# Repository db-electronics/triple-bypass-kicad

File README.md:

# Triple Bypass Version 2
This is a redesign of the fantastic 3bp from dbElectronics.  The goal of this project was to take the initial design and accommodate all models on one pcb without the need to swap parts. It was a team effort between myself, Retrorgb, and Jose Cruz who did the majorty of the testing. Ace, FirebrandX and Mobiusstriptech all were part of the group that helped with the redesign and added various ideas and suggestions that lead to the final product.  The audio adjustment work was done with the help of the mdFourier tool by Artemio Urbina found here - 
https://github.com/ArtemioUrbina/MDFourier.  Artemio and Bfbii stayed up many late nights and helped me run mdFourier to get the levels to match as close as we could to a model 1 va3 genesis.

# Installation Instructions

Currently I suggest using the Audio installation instructions from the mega amp 2.0
http://www.sega-16.com/forum/showthread.php?31989-Take-your-Genesis-audio-to-the-next-level-The-Mega-Amp-2-0-is-here!

For rgb bypass instructions, please see https://www.retrorgb.com/genesistriplebypass.html for now. I will continue working on getting more up-to-date instructions.

# Confirmed Working
The current version of this is working with no issues and has been tested and measured with mdFourier. There are still some systems where the pull down jumpers have not been confirmed.  If you notice any issues, please let me know.
# Design Files
I designed this using the online software tool Easyeda. While I have made the file open for people to edit, I have not yet been able to allow for the files to be truly open source.  This is a work in progress and if I have to remake everything from scratch in Kicad. The files here will always be the most up to date versions. 
# Change Log 17/03/2020
I have added a kicad file to the folder.  it looks ok but I still see some issues with ground layers.  I am new to kicad but this pretty damn close.  As it stands, I still recommend using the current gerber files to send to a pcd fab.  The design files are good to go if you want to to change or modify the design.  
# Change Log 06/03/2020
- Changed the jumper settings on the silk screen to match new info from Jose Cruz that the model 2 va4 has all of the 75 ohm pulldowns on the Genesis. Nothing needs to be changed on the previous versions.  Just take note when installing in a model 2 va4.
# Change Log from V1
 - Added jumpers so that all pulldowns could be enabled or disabled without switching parts.
 - Added AC coupling capacitors on the input of the ths7374 to accommodate for systems that we have not measured or installed in yet.
 - Changed the op amp to a soic8 footprint to accommodate a larger variety of possible op amps.
 - Changed the op amp to a tl972 low noise op amp.
 - Lowered the overall volume and increased resistance to try and alleviate some of the clipping in the louder games.
 - Changed the resistor values and numbering to try and fit on the smaller board.
 - Changed audio and video capacitors to tantalum to accommodate for a bottom mount. 
 - Adjusted and tested installation in a model 1 Genesis. 
 - Increased the audio output capacitors to 47uf.
 - Shrunk the overall size and move the din to the middle of the board to try to avoid the power jacks on a bottom install. 
 - Changed the Low pass filter to a solder jumper that will enable when it is jumped.

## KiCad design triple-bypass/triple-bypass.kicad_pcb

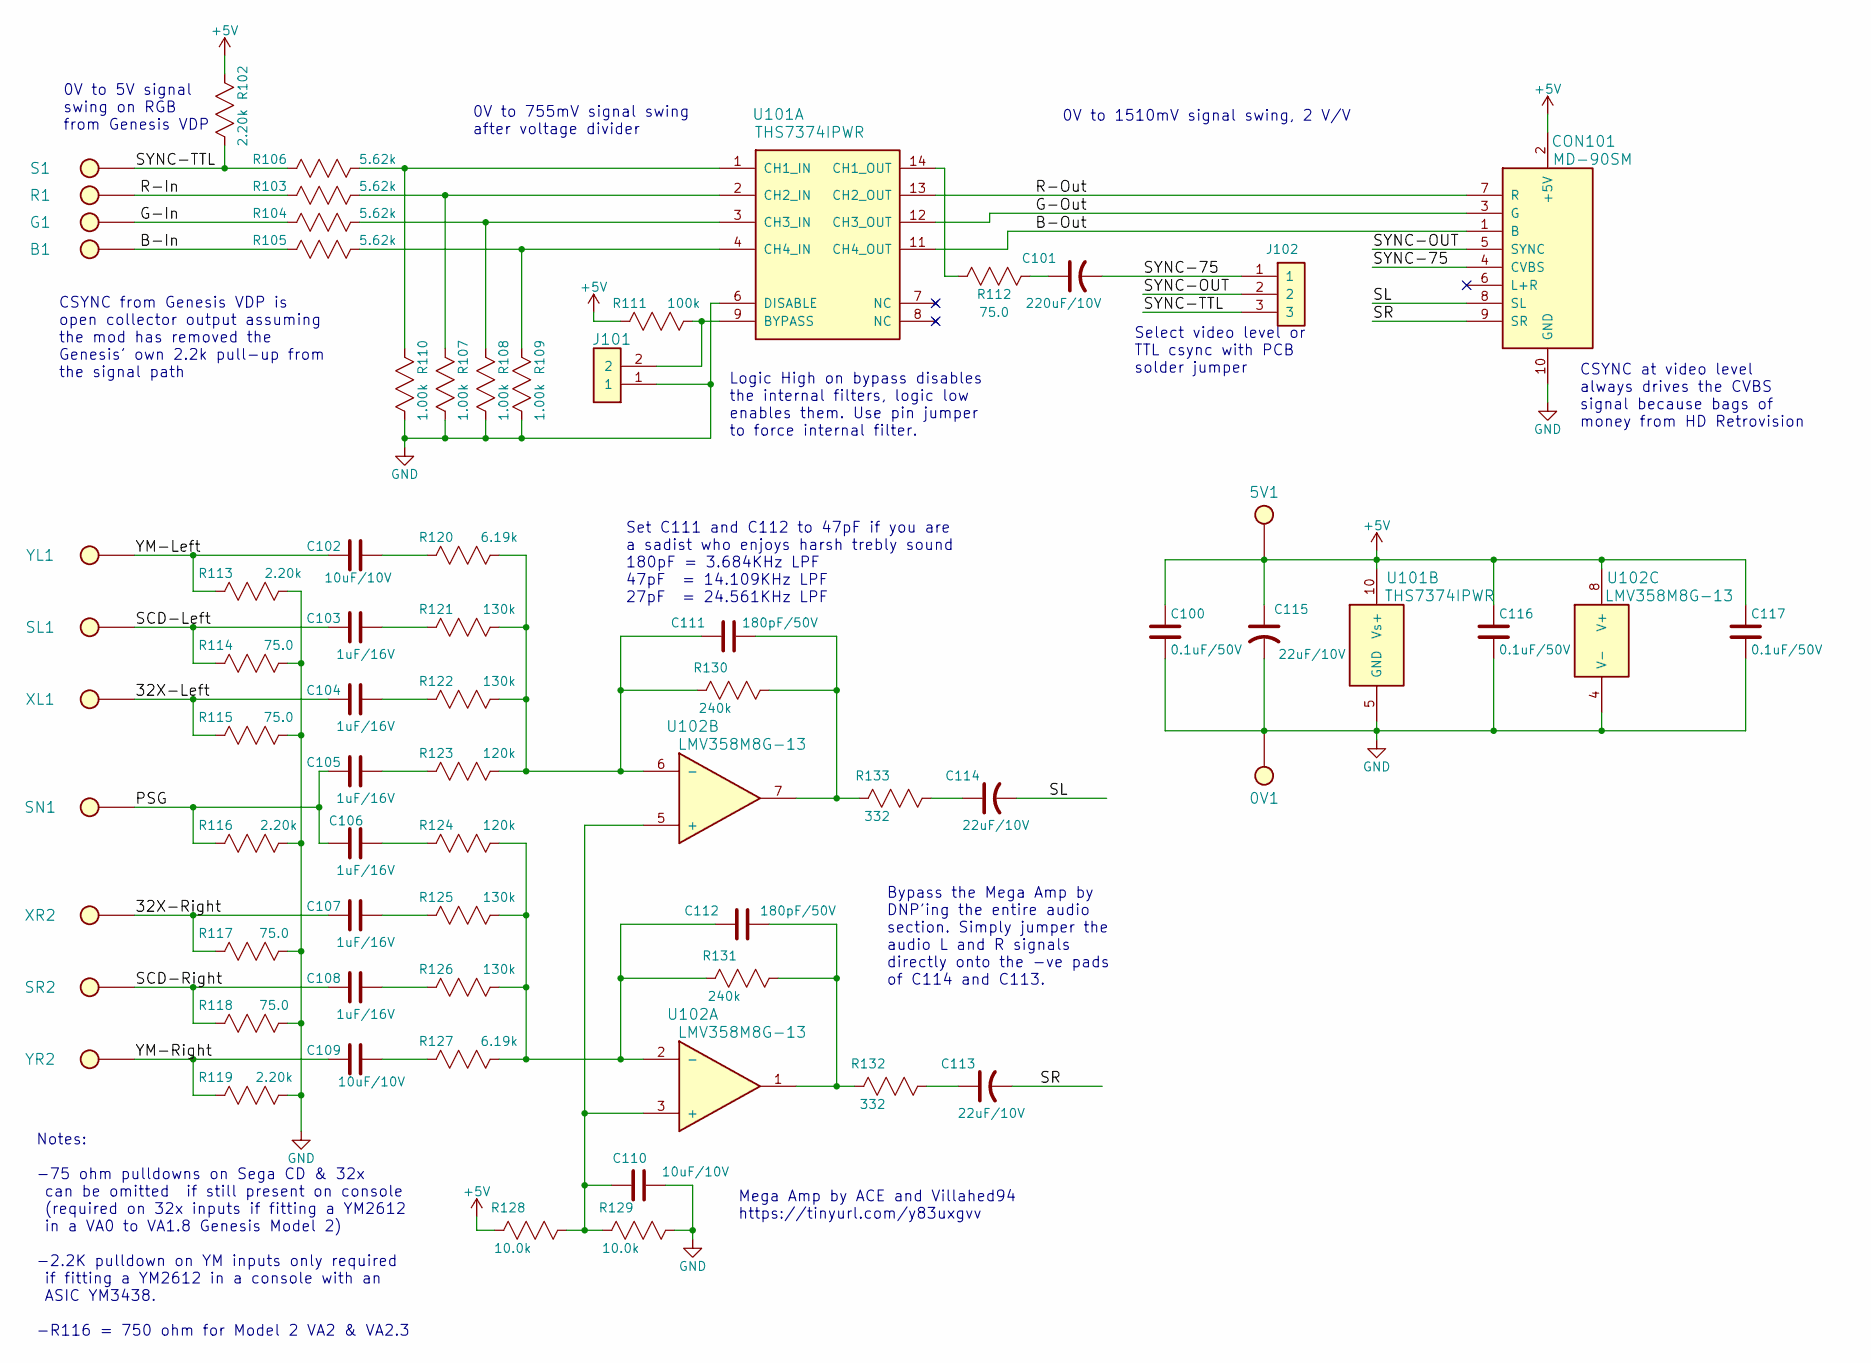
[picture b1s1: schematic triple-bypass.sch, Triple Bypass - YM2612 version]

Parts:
0V1, 5V1: TP_50; TP50; Digikey #ND
B1: TP_50; TP50; Digikey #ND
C100, C116, C117: 0.1uF/50V; 0603; Digikey 445-5666-1-ND
C101: 220uF/10V; SMD-6.6x6.6; Digikey 493-6210-1-ND
C102, C109, C110: 10uF/10V; 0805; Digikey 311-1460-1-ND
C103, C104, C105, C106, C107, C108: 1uF/16V; 0603; Digikey 445-1416-1-ND
C111, C112: 180pF/50V; 0603; Digikey 311-4096-6-ND
C113, C114, C115: 22uF/10V; 1206_P; Digikey 478-1663-1-ND
CON101: MD-90SM; Digikey CP-2290-ND
G1: TP_50; TP50; Digikey #ND
J101: HDR1X2; Digikey 952-2262-ND
J102: JMP-PCB-3POS
R1: TP_50; TP50; Digikey #ND
R102, R113, R116, R119: 2.20k; 0603; Digikey P2.20KHCT-ND
R103, R104, R105, R106: 5.62k; 0603; Digikey P5.62KHCT-ND
R107, R108, R109, R110: 1.00k; 0603; Digikey P1.00KHCT-ND
R111: 100k; 0603; Digikey RHM100KAYCT-ND
R112, R114, R115, R117, R118: 75.0; 0603; Digikey P75.0HCT-ND
R120, R127: 6.19k; 0603; Digikey P6.19KHCT-ND
R121, R122, R125, R126: 130k; 0603; Digikey P130KHCT-ND
R123, R124: 120k; 0603; Digikey P120KHCT-ND
R128, R129: 10.0k; 0603; Digikey P10.0KHCT-ND
R130, R131: 240k; 0603; Digikey P240KHCT-ND
R132, R133: 332; 0603; Digikey P332HCT-ND
S1: TP_50; TP50; Digikey #ND
SL1: TP_50; TP50; Digikey #ND
SN1: TP_50; TP50; Digikey #ND
SR2: TP_50; TP50; Digikey #ND
U101: THS7374IPWR; TSSOP-14; Digikey 296-41661-1-ND
U102: LMV358M8G-13; TSSOP-8_3.0mm; Digikey LMV358M8G-13DITR-ND
XL1: TP_50; TP50; Digikey #ND
XR2: TP_50; TP50; Digikey #ND
YL1: TP_50; TP50; Digikey #ND
YR2: TP_50; TP50; Digikey #ND

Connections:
+5V: 5V1.1, C100.1, C115.1, C116.1, C117.1, CON101.2 (+5V), R102.2, R111.1, R128.1, U101.10 (Vs+), U102.8 (V+)
/32X-Left: C104.1, R115.1, XL1.1
/32X-Right: C107.1, R117.1, XR2.1
/B-In: B1.1, R105.2
/B-Out: CON101.1 (B), U101.11 (CH4_OUT)
/G-In: G1.1, R104.2
/G-Out: CON101.3 (G), U101.12 (CH3_OUT)
/PSG: C105.1, C106.1, R116.1, SN1.1
/R-In: R1.1, R103.2
/R-Out: CON101.7 (R), U101.13 (CH2_OUT)
/SCD-Left: C103.1, R114.1, SL1.1
/SCD-Right: C108.1, R118.1, SR2.1
/SL: C114.2, CON101.8 (SL)
/SR: C113.2, CON101.9 (SR)
/SYNC-75: C101.2, CON101.4 (CVBS), J102.1
/SYNC-OUT: CON101.5 (SYNC), J102.2
/SYNC-TTL: J102.3, R102.1, R106.2, S1.1
/YM-Left: C102.2, R113.1, YL1.1
/YM-Right: C109.2, R119.1, YR2.1
GND: 0V1.1, C100.2, C110.1, C115.2, C116.2, C117.2, CON101.10 (GND), J101.1, R107.1, R108.1, R109.1, R110.1, R113.2, R114.2, R115.2, R116.2, R117.2, R118.2, R119.2, R129.2, U101.5 (GND), U101.6 (DISABLE), U102.4 (V-)
unnamed: C101.1, R112.1
unnamed: C102.1, R120.1
unnamed: C103.2, R121.1
unnamed: C104.2, R122.1
unnamed: C105.2, R123.1
unnamed: C106.2, R124.1
unnamed: C107.2, R125.1
unnamed: C108.2, R126.1
unnamed: C109.1, R127.1
unnamed: C110.2, R128.2, R129.1, U102.3 (+), U102.5 (+)
unnamed: C111.1, R120.2, R121.2, R122.2, R123.2, R130.1, U102.6 (-)
unnamed: C111.2, R130.2, R133.1, U102.7 (OUTB)
unnamed: C112.1, R124.2, R125.2, R126.2, R127.2, R131.1, U102.2 (-)
unnamed: C112.2, R131.2, R132.1, U102.1 (OUTA)
unnamed: C113.1, R132.2
unnamed: C114.1, R133.2
unnamed: J101.2, R111.2, U101.9 (BYPASS)
unnamed: R103.1, R107.2, U101.2 (CH2_IN)
unnamed: R104.1, R108.2, U101.3 (CH3_IN)
unnamed: R105.1, R109.2, U101.4 (CH4_IN)
unnamed: R106.1, R110.2, U101.1 (CH1_IN)
unnamed: R112.2, U101.14 (CH1_OUT)

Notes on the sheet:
Logic High on bypass disables the internal filters, logic low enables them. Use pin jumper to force internal filter.
Select video level or TTL csync with PCB solder jumper
CSYNC at video level always drives the CVBS signal because bags of money from HD Retrovision
0V to 5V signal swing on RGB from Genesis VDP
0V to 755mV signal swing after voltage divider
CSYNC from Genesis VDP is open collector output assuming the mod has removed the Genesis' own 2.2k pull-up from the signal path
0V to 1510mV signal swing, 2 V/V
Mega Amp by ACE and Villahed94 https://tinyurl.com/y83uxgvv
Set C111 and C112 to 47pF if you are a sadist who enjoys harsh trebly sound 180pF = 3.684KHz LPF 47pF = 14.109KHz LPF 27pF = 24.561KHz LPF
Bypass the Mega Amp by DNP'ing the entire audio section. Simply jumper the audio L and R signals directly onto the -ve pads of C114 and C113.
Notes: -75 ohm pulldowns on Sega CD & 32x can be omitted if still present on console (required on 32x inputs if fitting a YM2612 in a VA0 to VA1.8 Genesis Model 2) -2.2K pulldown on YM inputs only required if fitting a YM2612 in a console with an ASIC YM3438. -R116 = 750 ohm for Model 2 VA2 & VA2.3

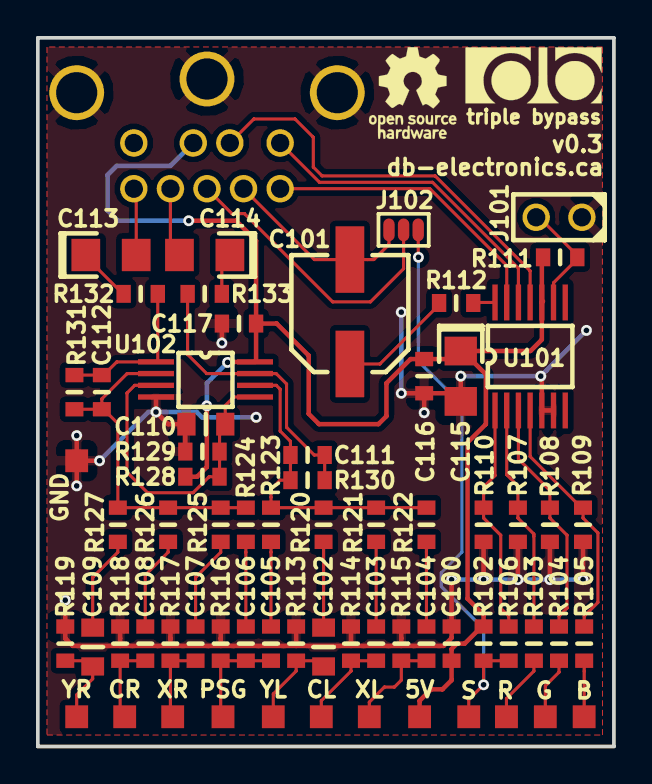
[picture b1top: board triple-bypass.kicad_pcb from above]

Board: 2 copper layers, 32.0 x 39.4 mm, 68 parts (1 on the bottom side), 42 nets.

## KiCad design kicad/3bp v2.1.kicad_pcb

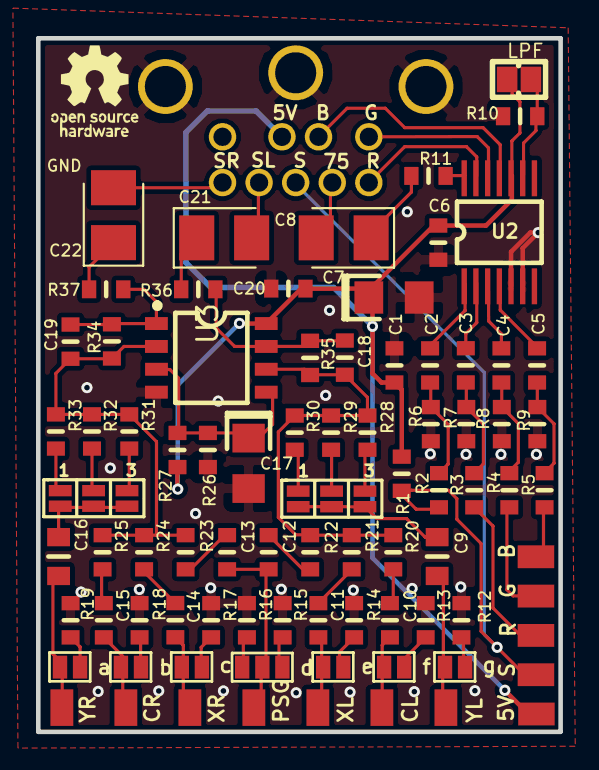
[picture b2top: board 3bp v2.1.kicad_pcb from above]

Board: 2 copper layers, 29.0 x 38.5 mm, 86 parts (0 on the bottom side), 23 nets.

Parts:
1, 1#2: 3; JUMPER
5V1: TP_50; TP50
B1: TP_50; TP50
C1, C6, C20: 0.1uF/50V; 0603
C2, C3, C4, C5, C18, C19: 270pF/50V; 0603
C7, C17: 22uF/10V; 1206_P
C8, C21, C22: CP_TANTALUM_CASE-B_EIA-3528-21_REFLOW
C9, C16: 0805
C10, C11, C12, C13, C14, C15: 1uF/16V; 0603
CON1: MD-90SM
G: LOGO; OSHW-LOGO_5MM
G1: TP_50; TP50
G#2: LOGO; OSHW-LOGO_5MM
JP1: JUMPER_SOLDER_1X2
R1: TP_50; TP50
R1#2, R12, R19: 2.20k; 0603
R2, R3, R4, R5: 5.62k; 0603
R6, R7, R8, R9, R10, R11: 1.00k; 0603
R13, R14, R15, R16, R17, R18: 75.0; 0603
R20, R21, R24, R25, R29, R30: 130k; 0603
R22, R23: 100k; 0603
R26, R27: 10.0k; 0603
R28, R31, R32, R33: 6.19k; 0603
R34, R35: 162k; 0603
R36, R37: 332; 0603
S1: TP_50; TP50
SL1: TP_50; TP50
SN1: TP_50; TP50
SR2: TP_50; TP50
U2: THS7374IPWR; TSSOP-14
U3: DMP-8
XL1: TP_50; TP50
XR2: TP_50; TP50
YL1: TP_50; TP50
YR2: TP_50; TP50
a: JUMPER_PADSX2
b: JUMPER_PADSX2
c: JUMPER_PADSX2
d: JUMPER_PADSX3
e: JUMPER_PADSX2
f: JUMPER_PADSX2
g: JUMPER_PADSX2

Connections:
32X-LEFT: C11.1, C11.2, R14.1, R21.1, SL1.1, e.1, e.2
32X-RIGHT: C14.1, C14.2, R17.1, R24.1, XR2.1, c.1, c.2
+5V: 5V1.1, C1.1, C6.1, C7.1, C20.1, CON1.2, JP1.1, R1#2.2, R27.1, U2.10, U3.8
B-IN: B1.1, C5.1, C5.2, R5.1, R5.2, R9.2, U2.4
B-OUT: CON1.1, U2.11
G-IN: C4.1, C4.2, G1.1, R4.1, R4.2, R8.2, U2.3
G-OUT: CON1.3, U2.12
GND: C1.2, C6.2, C7.2, C17.2, C20.2, CON1.10, R6.1, R7.1, R8.1, R9.1, R10.1, R12.2, R13.2, R14.2, R15.2, R16.2, R17.2, R18.2, R19.2, R26.1, U2.5, U2.6, U3.4
LEFT: C18.1, C18.2, R20.2, R21.2, R22.2, R28.2, R29.2, R30.2, R35.1, R35.2, R36.2, U3.6, U3.7
LPF: JP1.2, R10.2, U2.9
PSG: C12.1, C12.2, C13.1, C13.2, R15.1, R16.1, R22.1, R23.1, SN1.1, d.1, d.2, d.3
R-IN: C3.1, C3.2, R1.1, R3.1, R3.2, R7.2, U2.2
R-OUT: CON1.7, U2.13
RIGHT: C19.1, C19.2, R23.2, R24.2, R25.2, R31.2, R32.2, R33.2, R34.1, R34.2, R37.1, U3.1, U3.2
S$33979: C17.1, R26.2, R27.2, U3.3, U3.5
SCD-LEFT: C10.1, C10.2, R13.1, R20.1, XL1.1, f.1, f.2
SCD-RIGHT: C15.1, C15.2, R18.1, R25.1, SR2.1, b.1, b.2
SL: C21.1, C21.2, CON1.8, R36.1
SR: C22.1, C22.2, CON1.9, R37.2
SYNC-75: C8.2, CON1.4
SYNC-OUT: C2.1, C2.2, C8.1, CON1.5, R1#2.1, R2.1, R2.2, R6.2, R11.1, R11.2, S1.1, U2.1, U2.14
YM-LEFT: 1.1, 1.2, C9.1, C9.2, R12.1, R28.1, R29.1, R30.1, YL1.1, g.1, g.2
YM-RIGHT: 1#2.1, 1#2.2, C16.1, C16.2, R19.1, R31.1, R32.1, R33.1, YR2.1, a.1, a.2

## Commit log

2018-01-24 added license
2018-01-24 building the schematic
2018-01-26 first pass schematic done, not annotated yet
2018-01-27 finalized and annotated schematic, waiting for review
2018-08-01 added parts to PCB
2018-08-01 more parts placement
2018-08-01 v0.3 prelim routing complete, sch added
2018-08-01 rotated sch 90 degrees
2018-08-02 changed csync routing to pins 1/14 on 7374
2018-08-07 Update to Mega Amp 2.0 and generated 3 seperated BOMs/SCH
2018-10-11 fixed R116 in BOM - 2.20k instead of 1.30k
2018-11-12 fixed BOM mistake - R123,R124 changed to 75.0k on YM3438-GOAC version
2020-03-05 Create Schematics
2020-03-05 Rename 3bp v2. copy.json to json_file/3bp v2. copy.json
2020-03-05 Rename 3bp v2. copy.json to 3bp v2.json
2020-03-05 Rename Triple Bypass v2.json to json_file/Triple Bypass v2 sch.json
2020-03-05 /schematics/
2020-03-26 Better version with ground connected

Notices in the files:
kicad/3bp v2.1.kicad_pcb:
Licensed under CERN OHL v.1.2
